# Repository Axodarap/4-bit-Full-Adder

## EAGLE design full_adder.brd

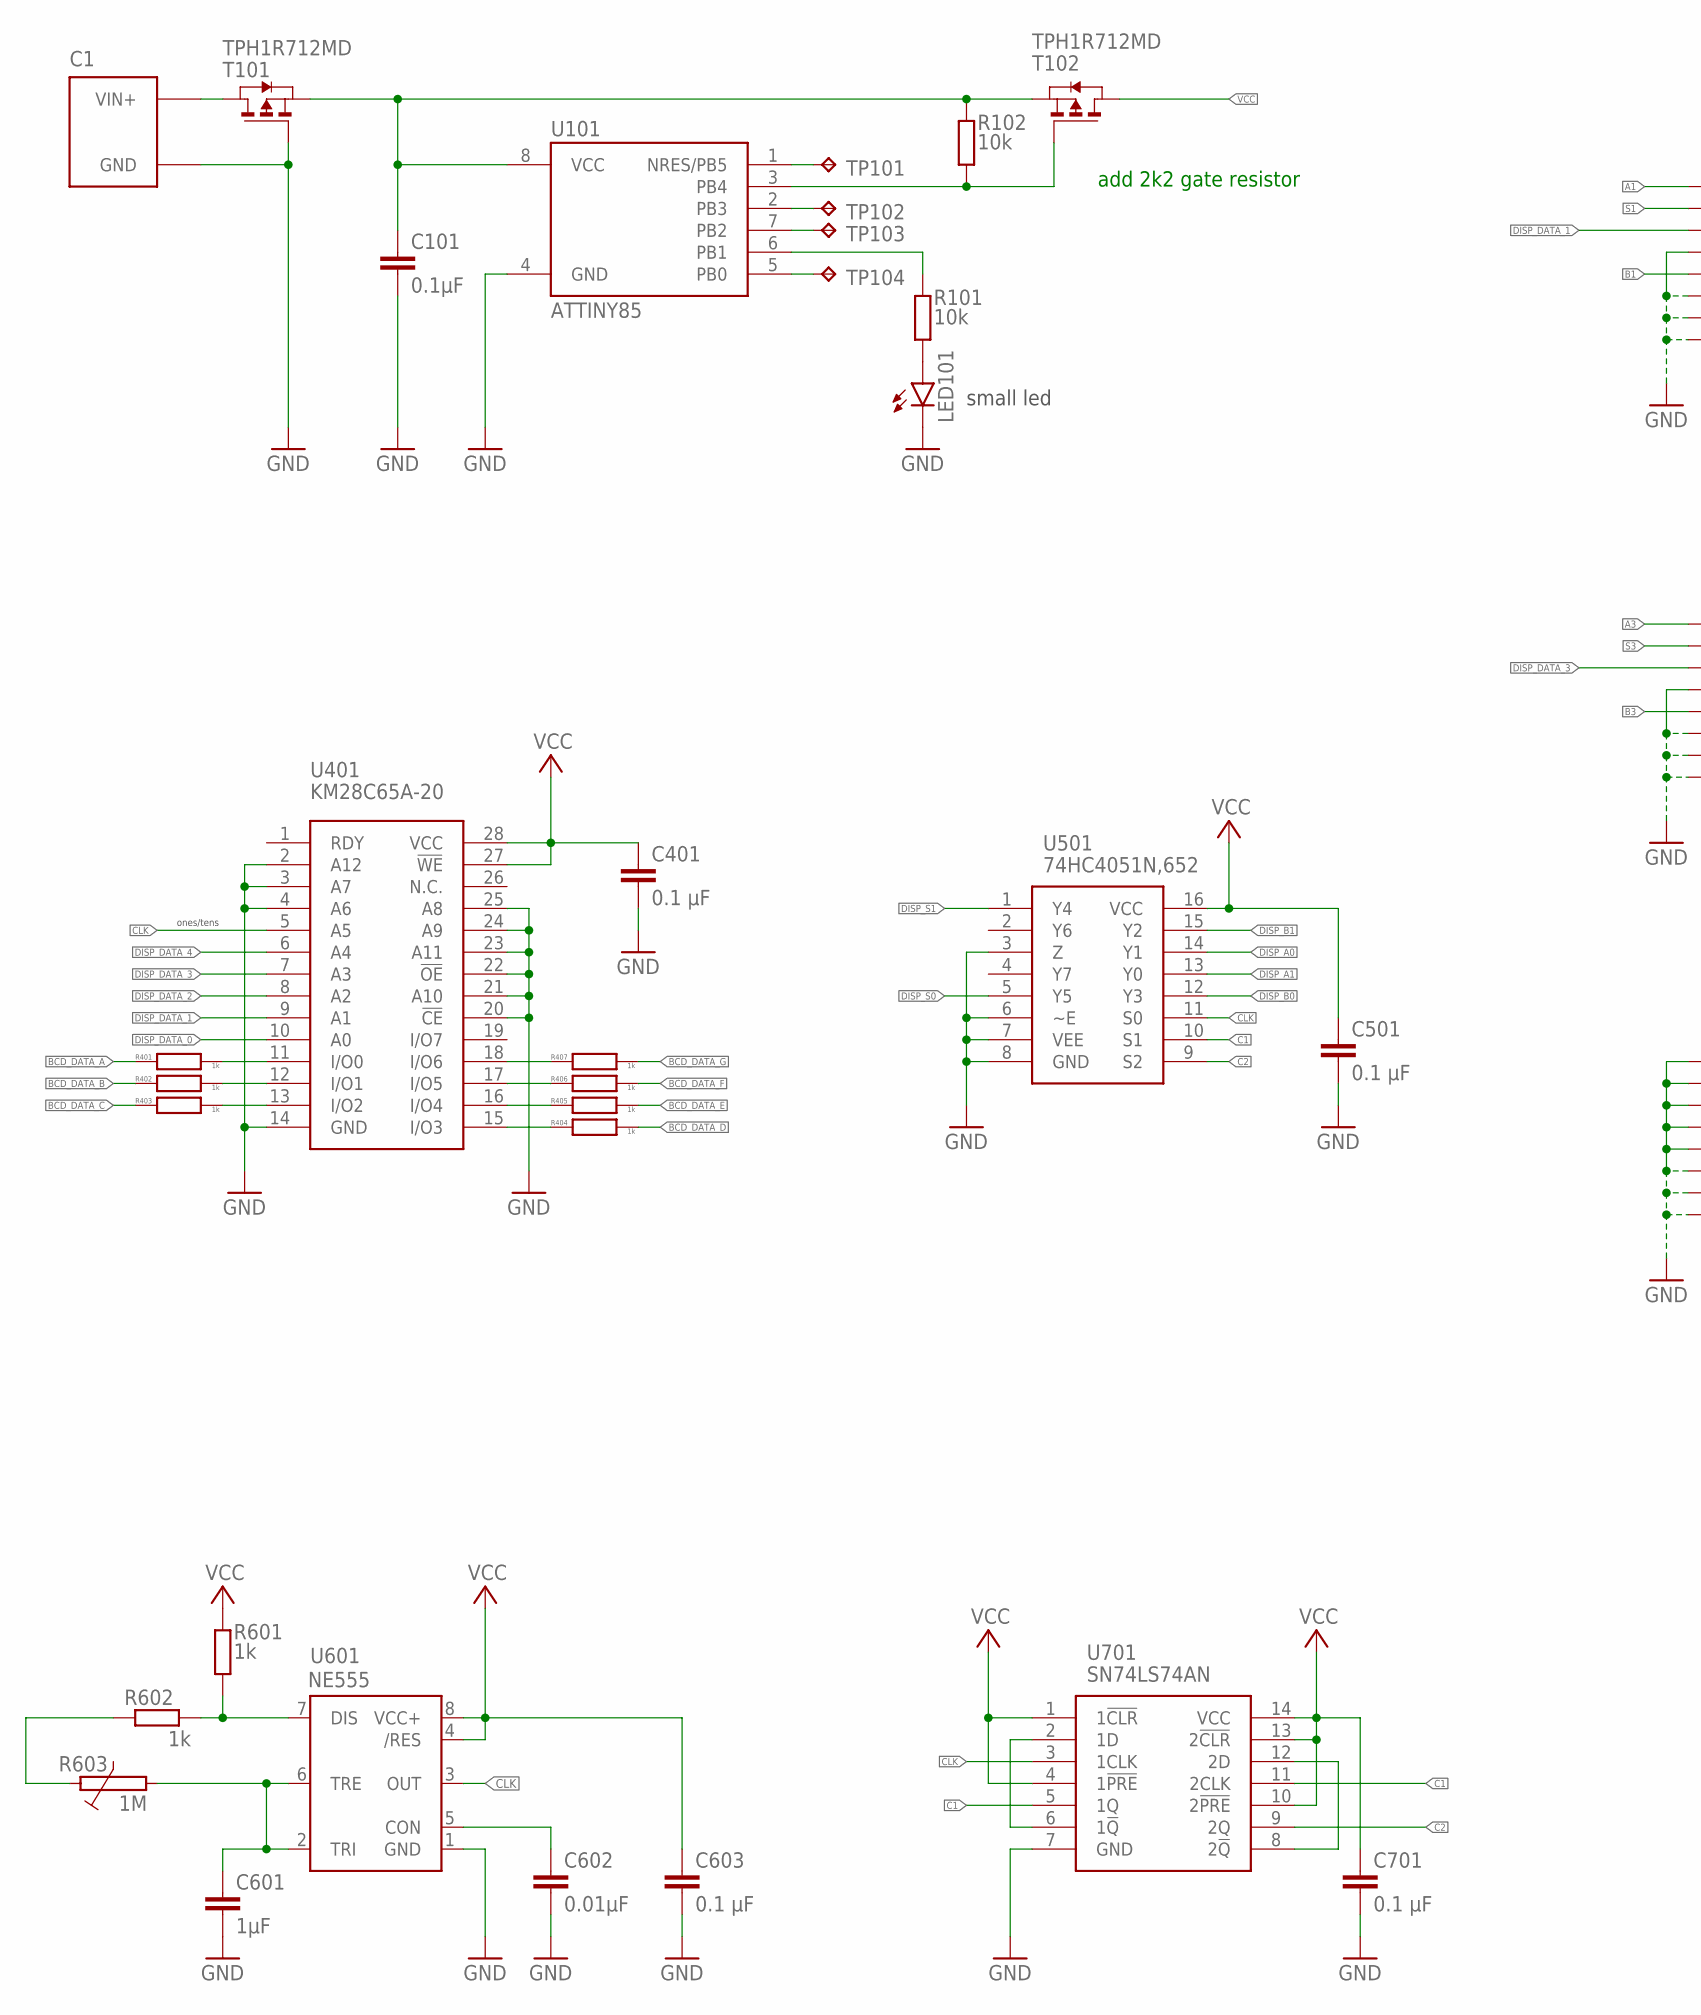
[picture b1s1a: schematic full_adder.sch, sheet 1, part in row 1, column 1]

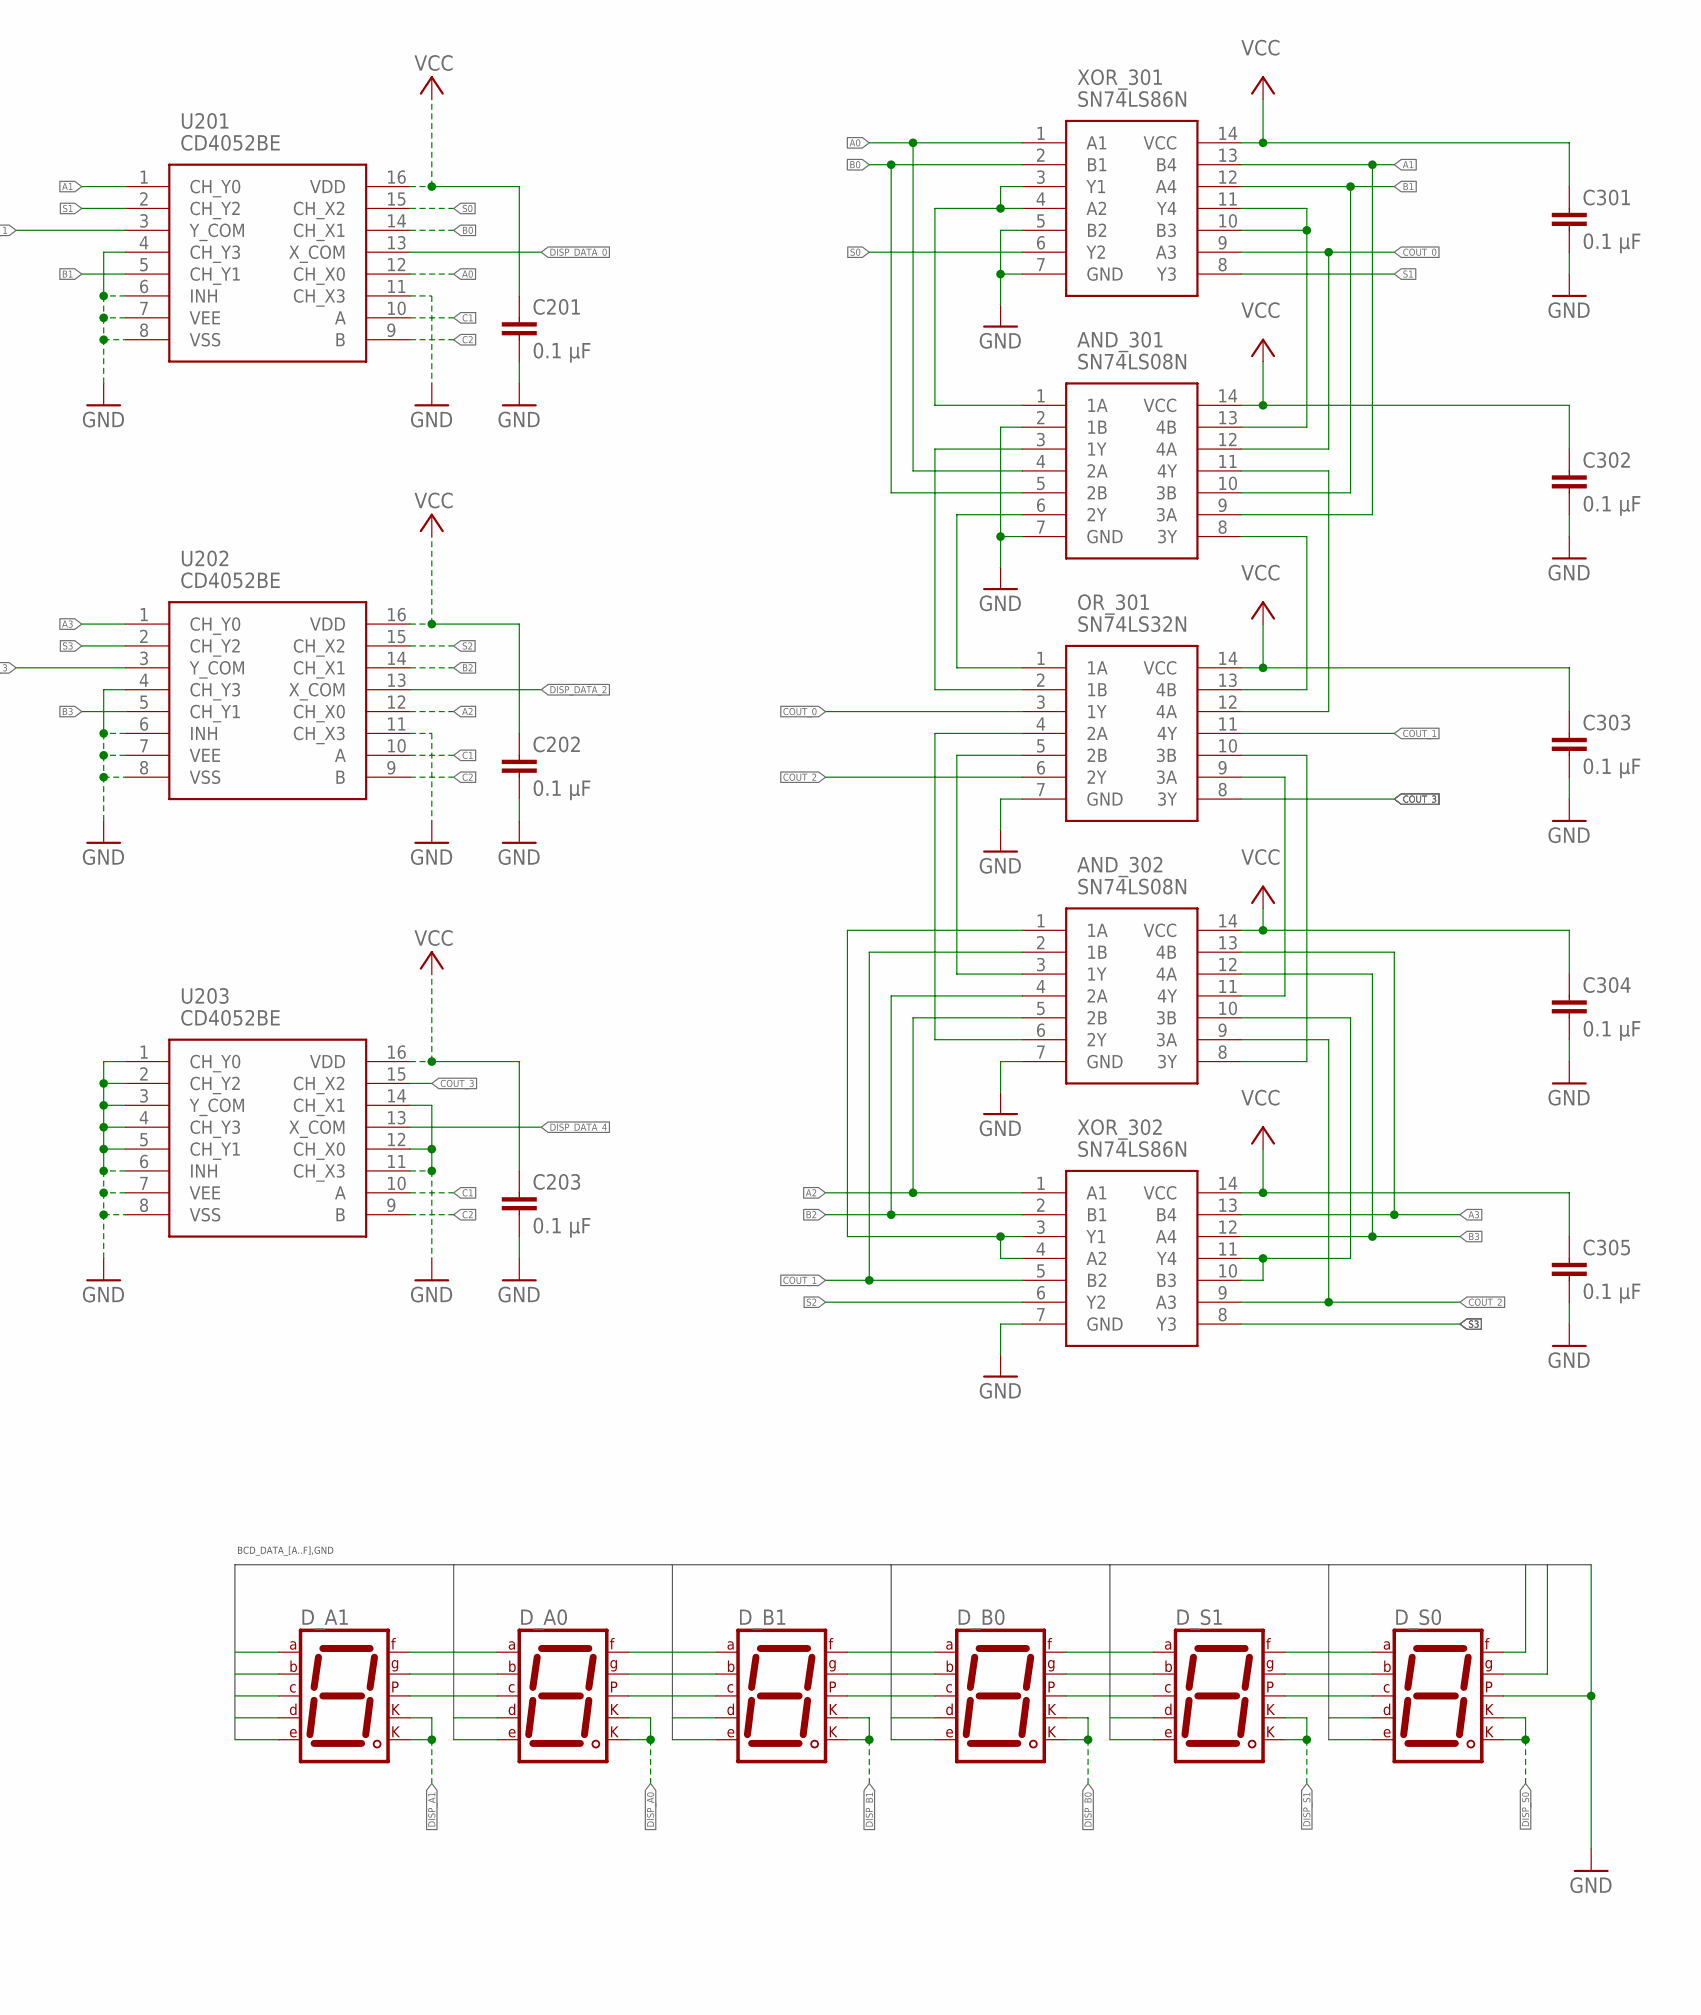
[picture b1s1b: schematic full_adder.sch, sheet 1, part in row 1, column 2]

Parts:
AND_301, AND_302: SN74LS08N; DIP794W53P254L1930H508Q14N
C1: BATTERY_CONNECTOR
C101: 0.1µF; C1206
C201, C202, C203, C301, C302, C303, C304, C305, C401, C501, C603, C701: 0.1 µF; C1206
C601: 1µF; C050-024X044
C602: 0.01µF; C050-024X044
D_A0, D_A1: 7SEG-CK; 7SEG-13
D_B0, D_B1: 7SEG-CK; 7SEG-13
D_S0, D_S1: 7SEG-CK; 7SEG-13
LED101: LED3MM
OR_301: SN74LS32N; DIP794W53P254L1930H508Q14N
R101, R102: 10k; R1206
R401, R402, R403, R404, R405, R406, R407, R601, R602: 1k; R1206
R603: 1M; POTENTIOMETER
T101, T102: TPH1R712MD; TPH1R712MDL1Q
TP101, TP102, TP103, TP104: TPB2,54; B2,54
U101: ATTINY85; PDIP08_300MIL
U201, U202, U203: CD4052BE; DIP794W53P254L1930H508Q16N
U401: KM28C65A-20
U501: 74HC4051N,652; DIP254P762X420-16
U601: NE555; DIL-08
U701: SN74LS74AN; DIP794W53P254L1930H508Q14N
XOR_301, XOR_302: SN74LS86N; DIP762W53P254L1848H469Q14N

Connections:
A0: AND_301.4 (2A), U201.12 (CH_X0), XOR_301.1 (A1); also elsewhere on the board
A1: AND_301.9 (3A), U201.1 (CH_Y0), XOR_301.13 (B4); also elsewhere on the board
A2: AND_302.5 (2B), U202.12 (CH_X0), XOR_302.1 (A1); also elsewhere on the board
A3: AND_302.13 (4B), U202.1 (CH_Y0), XOR_302.13 (B4); also elsewhere on the board
B0: AND_301.5 (2B), U201.14 (CH_X1), XOR_301.2 (B1); also elsewhere on the board
B1: AND_301.10 (3B), U201.5 (CH_Y1), XOR_301.12 (A4); also elsewhere on the board
B2: AND_302.4 (2A), U202.14 (CH_X1), XOR_302.2 (B1); also elsewhere on the board
B3: AND_302.12 (4A), U202.5 (CH_Y1), XOR_302.12 (A4); also elsewhere on the board
BCD_DATA_A: D_A0.7 (A), D_A1.7 (A), D_B0.7 (A), D_B1.7 (A), D_S0.7 (A), D_S1.7 (A), R401.1
BCD_DATA_B: D_A0.6 (B), D_A1.6 (B), D_B0.6 (B), D_B1.6 (B), D_S0.6 (B), D_S1.6 (B), R402.1
BCD_DATA_C: D_A0.4 (C), D_A1.4 (C), D_B0.4 (C), D_B1.4 (C), D_S0.4 (C), D_S1.4 (C), R403.1
BCD_DATA_D: D_A0.2 (D), D_A1.2 (D), D_B0.2 (D), D_B1.2 (D), D_S0.2 (D), D_S1.2 (D), R404.2
BCD_DATA_E: D_A0.1 (E), D_A1.1 (E), D_B0.1 (E), D_B1.1 (E), D_S0.1 (E), D_S1.1 (E), R405.2
BCD_DATA_F: D_A0.9 (F), D_A1.9 (F), D_B0.9 (F), D_B1.9 (F), D_S0.9 (F), D_S1.9 (F), R406.2
BCD_DATA_G: D_A0.10 (G), D_A1.10 (G), D_B0.10 (G), D_B1.10 (G), D_S0.10 (G), D_S1.10 (G), R407.2
C1: U201.10 (A), U202.10 (A), U203.10 (A), U501.10 (S1), U701.5 (1Q), U701.11 (2CLK)
C2: U201.9 (B), U202.9 (B), U203.9 (B), U501.9 (S2), U701.9 (2Q)
CLK: U401.5 (A5), U501.11 (S0), U601.3 (OUT), U701.3 (1CLK)
COUT_0: AND_301.12 (4A), OR_301.3 (1Y), XOR_301.9 (A3)
COUT_1: AND_302.2 (1B), OR_301.11 (4Y), XOR_302.5 (B2)
COUT_2: AND_302.9 (3A), OR_301.6 (2Y), XOR_302.9 (A3)
COUT_3: OR_301.8 (3Y), U203.15 (CH_X2); also elsewhere on the board
DISP_A0: D_A0.3 (CK1), D_A0.8 (CK2), U501.14 (Y1)
DISP_A1: D_A1.3 (CK1), D_A1.8 (CK2), U501.13 (Y0)
DISP_B0: D_B0.3 (CK1), D_B0.8 (CK2), U501.12 (Y3)
DISP_B1: D_B1.3 (CK1), D_B1.8 (CK2), U501.15 (Y2)
DISP_DATA_0: U201.13 (X_COM), U401.10 (A0)
DISP_DATA_1: U201.3 (Y_COM), U401.9 (A1)
DISP_DATA_2: U202.13 (X_COM), U401.8 (A2)
DISP_DATA_3: U202.3 (Y_COM), U401.7 (A3)
DISP_DATA_4: U203.13 (X_COM), U401.6 (A4)
DISP_S0: D_S0.3 (CK1), D_S0.8 (CK2), U501.5 (Y5)
DISP_S1: D_S1.3 (CK1), D_S1.8 (CK2), U501.1 (Y4)
GND: AND_301.2 (1B), AND_301.7 (GND), AND_302.7 (GND), C1.GND, C101.2, C201.2, C202.2, C203.2, C301.2, C302.2, C303.2, C304.2, C305.2, C401.2, C501.2, C601.2, C602.2, C603.2, C701.2, D_A0.5 (DP), D_A1.5 (DP), D_B0.5 (DP), D_B1.5 (DP), D_S0.5 (DP), D_S1.5 (DP), LED101.K (C), OR_301.7 (GND), T101.4 (G), U101.4 (GND), U201.4 (CH_Y3), U201.6 (INH), U201.7 (VEE), U201.8 (VSS), U201.11 (CH_X3), U202.4 (CH_Y3), U202.6 (INH), U202.7 (VEE), U202.8 (VSS), U202.11 (CH_X3), U203.1 (CH_Y0), U203.2 (CH_Y2), U203.3 (Y_COM), U203.4 (CH_Y3), U203.5 (CH_Y1), U203.6 (INH), U203.7 (VEE), U203.8 (VSS), U203.11 (CH_X3), U203.12 (CH_X0), U203.14 (CH_X1), U401.2 (A12), U401.3 (A7), U401.4 (A6), U401.14 (GND), U401.20 (!CE), U401.21 (A10), U401.22 (!OE), U401.23 (A11), U401.24 (A9), U401.25 (A8), U501.3 (Z), U501.6 (~E), U501.7 (VEE), U501.8 (GND), U601.1 (GND), U701.7 (GND), XOR_301.5 (B2), XOR_301.7 (GND), XOR_302.7 (GND); also elsewhere on the board
unnamed: AND_301.1 (1A), XOR_301.3 (Y1), XOR_301.4 (A2)
unnamed: AND_301.6 (2Y), OR_301.1 (1A)
unnamed: AND_301.3 (1Y), OR_301.2 (1B)
unnamed: AND_301.13 (4B), XOR_301.10 (B3), XOR_301.11 (Y4)
unnamed: AND_301.8 (3Y), OR_301.13 (4B)
unnamed: AND_301.11 (4Y), OR_301.12 (4A)
unnamed: AND_302.1 (1A), XOR_302.3 (Y1), XOR_302.4 (A2)
unnamed: AND_302.3 (1Y), OR_301.5 (2B)
unnamed: AND_302.6 (2Y), OR_301.4 (2A)
unnamed: AND_302.10 (3B), XOR_302.10 (B3), XOR_302.11 (Y4)
unnamed: C602.1, U601.5 (CON)
unnamed: AND_302.11 (4Y), OR_301.9 (3A)
unnamed: AND_302.8 (3Y), OR_301.10 (3B)
unnamed: C601.1, R603.POT$2, U601.2 (TRI), U601.6 (TRE)
unnamed: R602.1, R603.POT$1
unnamed: R601.1, R602.2, U601.7 (DIS)
unnamed: U701.8 (2!Q), U701.12 (2D)
unnamed: R101.2, U101.6 (PB1)
unnamed: TP101.TP, U101.1 (NRES/PB5)
unnamed: TP102.TP, U101.2 (PB3)
unnamed: TP103.TP, U101.7 (PB2)
unnamed: TP104.TP, U101.5 (PB0)
unnamed: C1.VIN+, T101.5 (D), T101.6 (D), T101.7 (D), T101.8 (D), T101.9 (D)
unnamed: C101.1, R102.2, T101.1 (S), T101.2 (S), T101.3 (S), T102.1 (S), T102.2 (S), T102.3 (S), U101.8 (VCC)
unnamed: R102.1, T102.4 (G), U101.3 (PB4)
unnamed: LED101.A, R101.1
unnamed: R401.2, U401.11 (I/O0)
unnamed: R402.2, U401.12 (I/O1)
unnamed: R403.2, U401.13 (I/O2)
unnamed: R407.1, U401.18 (I/O6)
unnamed: R406.1, U401.17 (I/O5)
unnamed: R405.1, U401.16 (I/O4)
unnamed: R404.1, U401.15 (I/O3)
unnamed: U701.2 (1D), U701.6 (1!Q)
S0: U201.15 (CH_X2), XOR_301.6 (Y2); also elsewhere on the board
S1: U201.2 (CH_Y2), XOR_301.8 (Y3); also elsewhere on the board
S2: U202.15 (CH_X2), XOR_302.6 (Y2); also elsewhere on the board
S3: U202.2 (CH_Y2), XOR_302.8 (Y3); also elsewhere on the board
VCC: AND_301.14 (VCC), AND_302.14 (VCC), C201.1, C202.1, C203.1, C301.1, C302.1, C303.1, C304.1, C305.1, C401.1, C501.1, C603.1, C701.1, OR_301.14 (VCC), R601.2, T102.5 (D), T102.6 (D), T102.7 (D), T102.8 (D), T102.9 (D), U201.16 (VDD), U202.16 (VDD), U203.16 (VDD), U401.27 (!WE), U401.28 (VCC), U501.16 (VCC), U601.4 (/RES), U601.8 (VCC+), U701.1 (1!CLR), U701.4 (1!PRE), U701.10 (2!PRE), U701.13 (2!CLR), U701.14 (VCC), XOR_301.14 (VCC), XOR_302.14 (VCC); also elsewhere on the board

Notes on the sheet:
ones/tens
BCD_DATA_[A..F],GND
small led
add 2k2 gate resistor

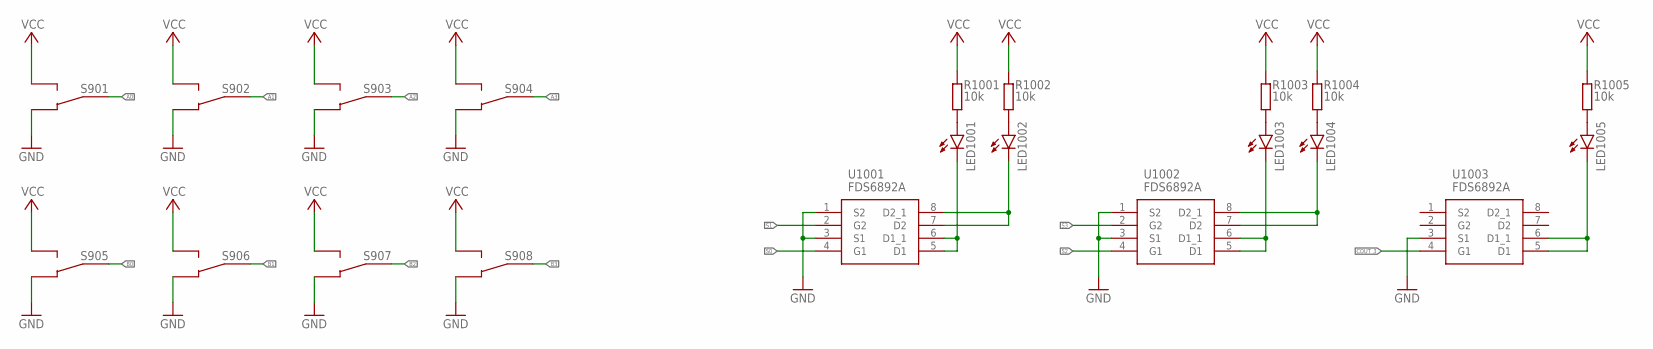
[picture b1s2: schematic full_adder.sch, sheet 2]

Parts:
LED1001, LED1002, LED1003, LED1004, LED1005: LED3MM
R1001, R1002, R1003, R1004, R1005: 10k; R1206
S901, S902, S903, S904, S905, S906, S907, S908: TOGGLESWITCH
U1001, U1002, U1003: FDS6892A; SOIC127P600X175-8N

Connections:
A0: S901.OUT (P$X); also elsewhere on the board
A1: S902.OUT (P$X); also elsewhere on the board
A2: S903.OUT (P$X); also elsewhere on the board
A3: S904.OUT (P$X); also elsewhere on the board
B0: S905.OUT (P$X); also elsewhere on the board
B1: S906.OUT (P$X); also elsewhere on the board
B2: S907.OUT (P$X); also elsewhere on the board
B3: S908.OUT (P$X); also elsewhere on the board
COUT_3: U1003.4 (G1); also elsewhere on the board
GND: S901.GND (P$A), S902.GND (P$A), S903.GND (P$A), S904.GND (P$A), S905.GND (P$A), S906.GND (P$A), S907.GND (P$A), S908.GND (P$A), U1001.1 (S2), U1001.3 (S1), U1002.1 (S2), U1002.3 (S1), U1003.3 (S1); also elsewhere on the board
unnamed: LED1001.A, R1001.1
unnamed: LED1002.A, R1002.1
unnamed: LED1003.A, R1003.1
unnamed: LED1004.A, R1004.1
unnamed: LED1005.A, R1005.1
unnamed: LED1001.K (C), U1001.5 (D1), U1001.6 (D1_1)
unnamed: LED1002.K (C), U1001.7 (D2), U1001.8 (D2_1)
unnamed: LED1003.K (C), U1002.5 (D1), U1002.6 (D1_1)
unnamed: LED1005.K (C), U1003.5 (D1), U1003.6 (D1_1)
unnamed: LED1004.K (C), U1002.7 (D2), U1002.8 (D2_1)
S0: U1001.4 (G1); also elsewhere on the board
S1: U1001.2 (G2); also elsewhere on the board
S2: U1002.4 (G1); also elsewhere on the board
S3: U1002.2 (G2); also elsewhere on the board
VCC: R1001.2, R1002.2, R1003.2, R1004.2, R1005.2, S901.VCC (P$B), S902.VCC (P$B), S903.VCC (P$B), S904.VCC (P$B), S905.VCC (P$B), S906.VCC (P$B), S907.VCC (P$B), S908.VCC (P$B); also elsewhere on the board

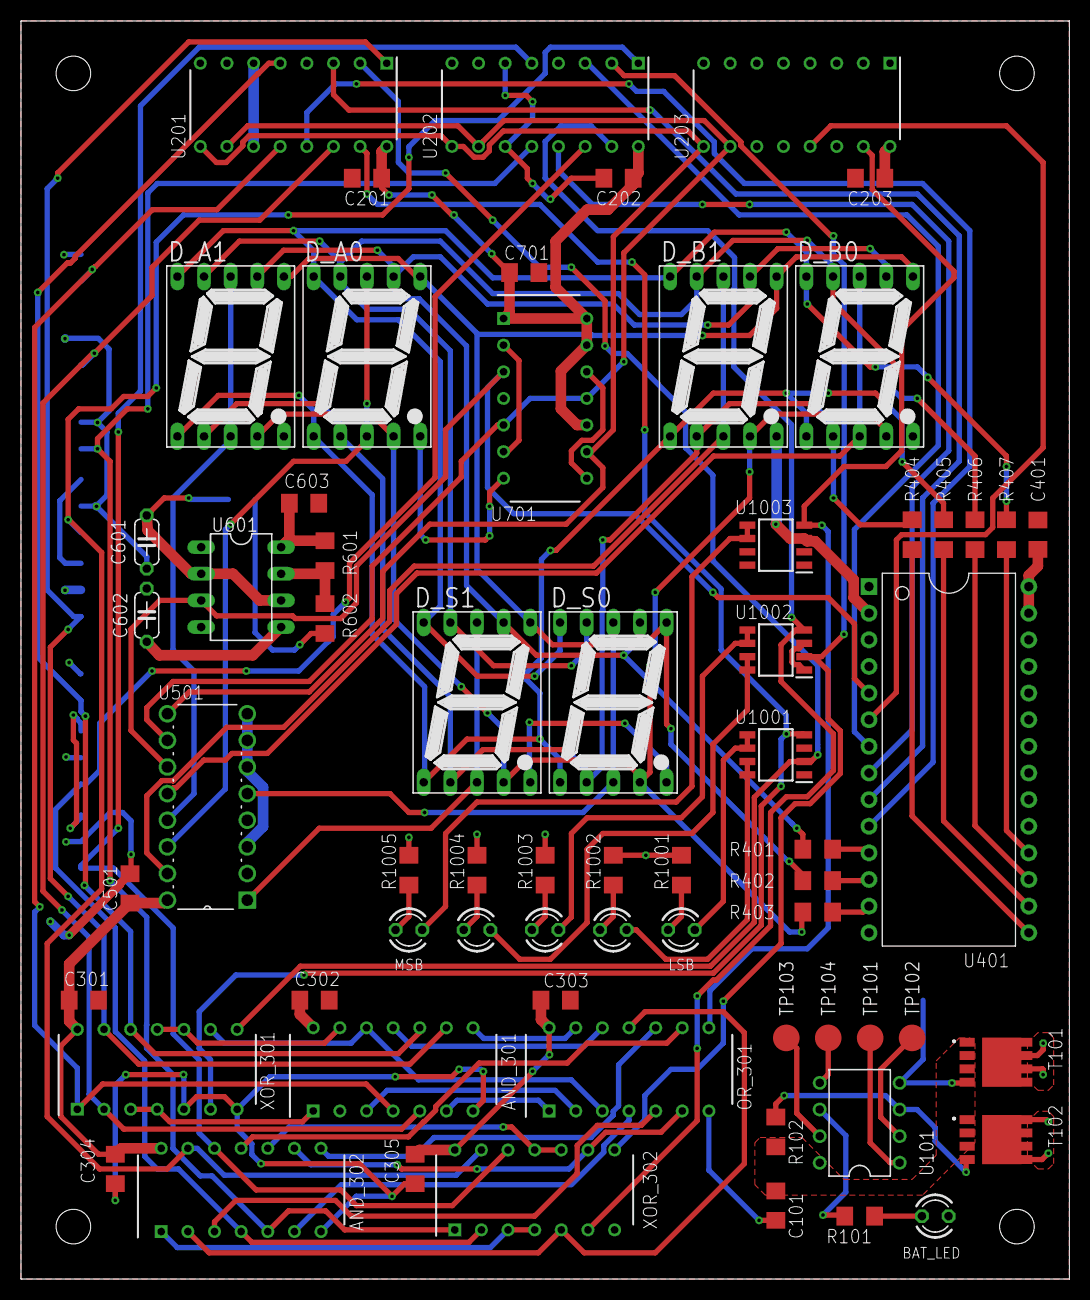
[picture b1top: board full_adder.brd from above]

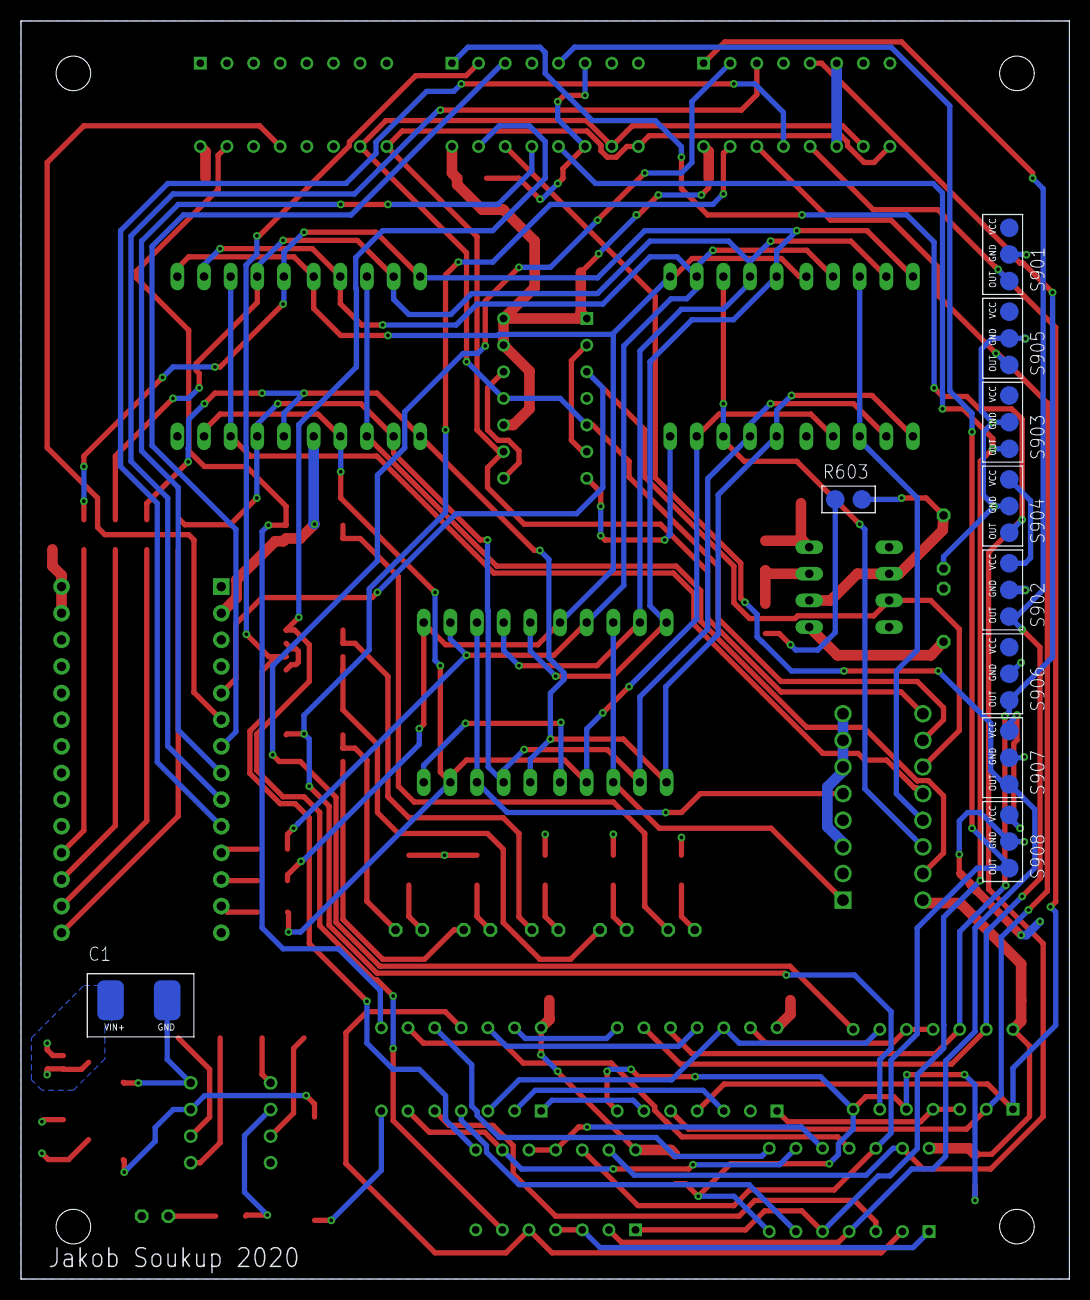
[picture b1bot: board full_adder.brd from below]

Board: 2 copper layers, 100.0 x 120.0 mm, 75 parts (10 on the bottom side), 83 nets.

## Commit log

2020-05-17 binary inputs and outputs added
2020-05-18 added support capacitors
2020-08-24 Added EEPROM resistors
2020-08-26 reverse polarity protection added
2020-09-17 basic input protection concept added
2020-09-24 minor fixes
2020-09-24 fet pulldown
2020-12-03 schematic verified
2020-12-03 finalization + cleanup
2020-12-03 cutoff fet --> p-channel
2020-12-03 minor
2020-12-04 p-channel footprint
2020-12-04 swapped capacitor footprints
2020-12-04 poti test pads
2020-12-04 fixed chaos
2020-12-05 swapped led footprints
2020-12-05 started layout
2020-12-05 basic layout complete
2020-12-06 Components placed
2020-12-06 routing v1 done
2020-12-06 drc errors, power planes
2020-12-06 fixing airwires
2020-12-07 DRC passed
2021-01-04 gate resistor
